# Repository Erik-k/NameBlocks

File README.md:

# NameBlocks
Small square boards which can be dynamically re-arranged to display a name in any arrangement

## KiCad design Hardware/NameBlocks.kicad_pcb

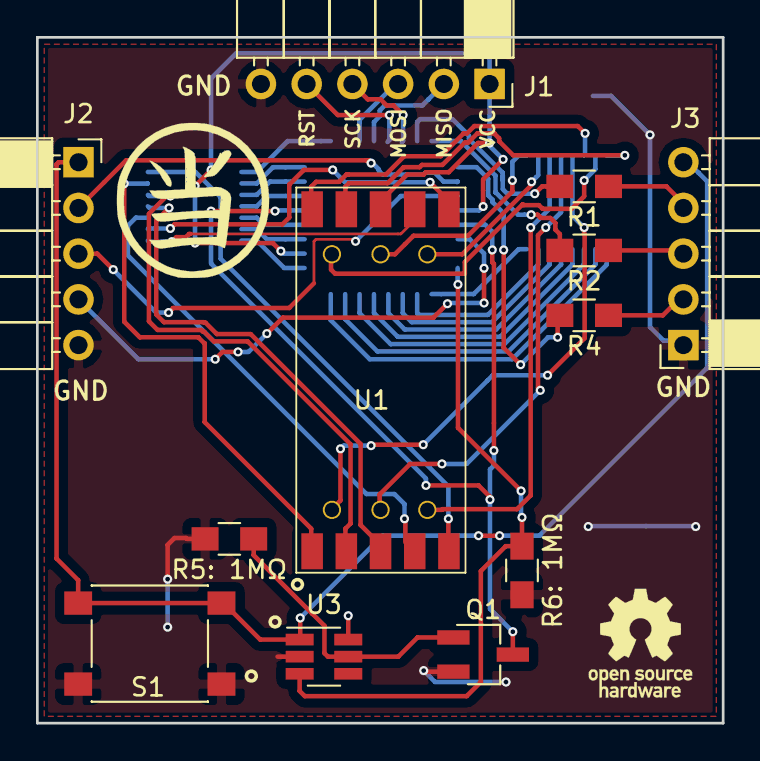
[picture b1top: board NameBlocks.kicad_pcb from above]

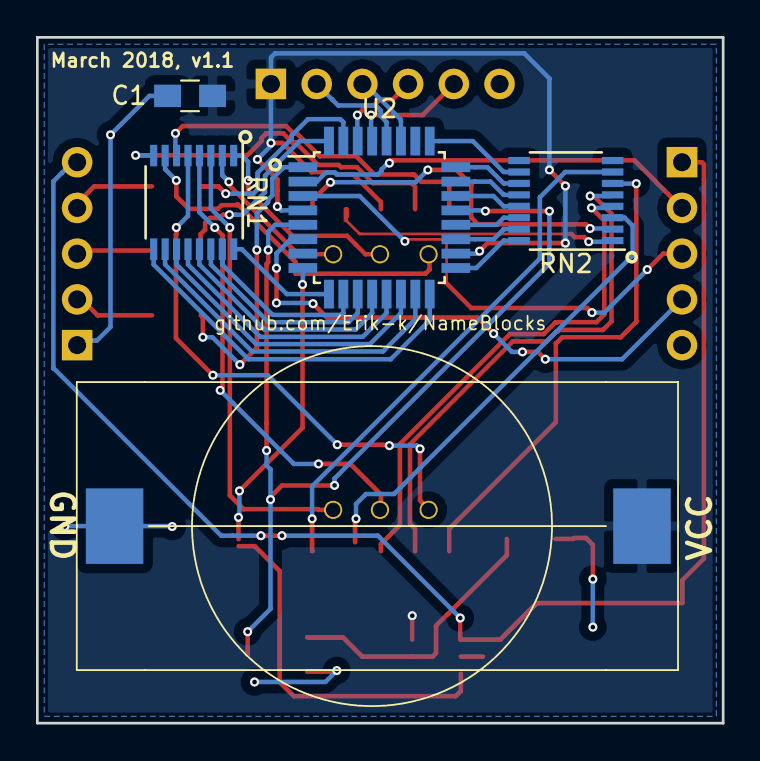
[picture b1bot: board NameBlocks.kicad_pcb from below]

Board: 2 copper layers, 38.1 x 38.1 mm, 17 parts (5 on the bottom side), 49 nets.

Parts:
BT1: Battery_Cell; CR2032_SMD_BatteryHolder_BU2032SM-BT-GTR
C1: 0.1u; C_0805_HandSoldering
J1: CONN_01X06; Socket_Strip_Angled_1x06_Pitch2.54mm
J2, J3: CONN_01X05; Socket_Strip_Angled_1x05_Pitch2.54mm
Q1: Q_NMOS_GSD; SC-59_Handsoldering
R1, R2, R4: 1k; R_0805_HandSoldering
R5: 1MΩ, R6: 1MΩ: 1M; R_0805_HandSoldering
RN1, RN2: 180; SSOP-16_3.9x4.9mm_Pitch0.635mm
S1: Button; SW_SPST_PTS645
U1: ACPSA04-41SRWA-17406; ACPSA04_Alphanumeric_LED
U2: ATTiny828; TQFP-32_7x7mm_Pitch0.8mm
U3: MAX16054; SOT-23-6_Handsoldering

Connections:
/Button: J2.1, J3.5, S1.3, S1.4, U3.1
/MISO: J1.2, U2.28
/MOSI: J1.3, U2.27
/PowerOFF: R6: 1MΩ.1, U2.8, U3.3
/RST: J1.5, U2.29
/SCK: J1.4, U2.30
/Signal_In_C3: J2.2, U2.2
/Signal_In_C4: J2.3, U2.3
/Signal_In_C5: J2.4, U2.6
/Signal_Out_C0: R1.2, U2.31
/Signal_Out_C1: R2.2, U2.32
/Signal_Out_C2: R4.2, U2.1
/uC_gnd: Q1.3, U2.5, U2.21
GND: BT1.2, C1.2, J1.6, J2.5, J3.1, Q1.2, R5: 1MΩ.2, R6: 1MΩ.2, S1.1, S1.2, U3.2
unnamed: J3.2, R4.1
unnamed: J3.3, R2.1
unnamed: J3.4, R1.1
unnamed: Q1.1, R5: 1MΩ.1, U3.5
unnamed: RN1.1, U1.10
unnamed: RN1.2, U1.11
unnamed: RN1.3, U1.6
unnamed: RN1.4, U1.7
unnamed: RN1.5, U1.8
unnamed: RN1.6, U1.16
unnamed: RN1.7, U1.9
unnamed: RN1.8, U1.15
unnamed: RN1.9, U2.16
unnamed: RN1.10, U2.15
unnamed: RN1.11, U2.14
unnamed: RN1.12, U2.13
unnamed: RN1.13, U2.12
unnamed: RN1.14, U2.11
unnamed: RN1.15, U2.10
unnamed: RN1.16, U2.9
unnamed: RN2.1, U1.13
unnamed: RN2.2, U1.12
unnamed: RN2.3, U1.4
unnamed: RN2.4, U1.3
unnamed: RN2.5, U1.2
unnamed: RN2.6, U1.1
unnamed: RN2.7, U1.5
unnamed: RN2.10, U2.25
unnamed: RN2.11, U2.24
unnamed: RN2.12, U2.23
unnamed: RN2.13, U2.22
unnamed: RN2.14, U2.20
unnamed: RN2.15, U2.19
unnamed: RN2.16, U2.17
VCC: BT1.1, C1.1, J1.1, U1.14, U2.4, U2.18, U3.6

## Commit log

2017-11-02 Add files via upload
    First commit. Choosing uC ...
2017-11-02 Add files via upload
    add .gitignore
2017-11-02 Create .gitignore
    First creation
2017-12-14 Add files via upload
    Created ATTiny828 part in KiCad
2017-12-19 Created Kingbright symbol, MAX16054 symbol
2017-12-21 Added 5 pin port, power switch IC
2018-01-11 Got the stoplight test working for three boards. Gotta remember |= vs &= !
2018-01-18 Finished schematic, all footprints and BOM chosen except switch.
    StopLightTest successful. Software is now going to be on hold until I get boards in.
2018-01-21 Finished all footprints. Time for layout!
    And I double checked the LED display footprint. Miraculous!
2018-01-21 Added button.lib
2018-01-31 Started layout. What a mess!
2018-02-01 Layout finished, but need silkscreen. Going to ask about mfg-ability
2018-02-20 Silkscreen done, ready for order
2018-02-21 Added dimension drawings
2018-02-21 Added MOSFET info to schematic, produced BOM
2018-03-05 Added silkscreen for JTAG programming pins
2018-03-20 Shrank trace on Net-(RN2-Pad1) for pin 13 of display
    Pins 13, 14, 15, 16 on the LED segment shorted together on two boards AFTER soldering the display down. I believe that is because trace Net-(RN2-Pad1) from pin 13 on the alphanumeric display was too 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
2018-03-20 Duplicate file
2018-03-20 Added note to fix TSSOP footprints
2018-03-20 Added note in layout to update TSSOP footprints
